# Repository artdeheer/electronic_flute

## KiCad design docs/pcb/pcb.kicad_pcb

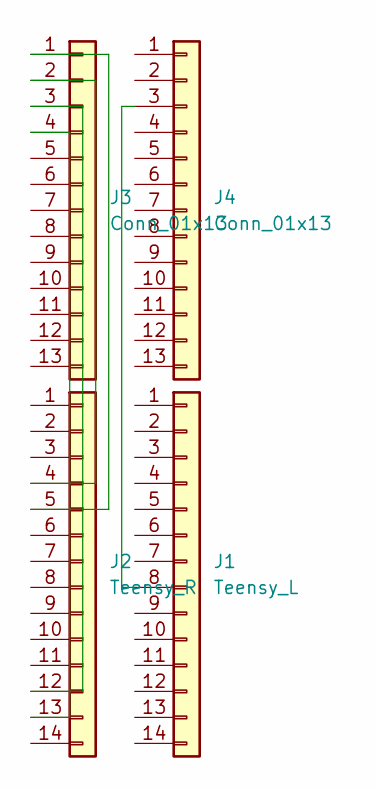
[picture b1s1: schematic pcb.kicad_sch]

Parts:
J1: Teensy_L; PinHeader_1x14_P2.54mm_Vertical
J2: Teensy_R; PinHeader_1x14_P2.54mm_Vertical
J3, J4: Conn_01x13; PinHeader_1x13_P2.54mm_Vertical

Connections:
unnamed: J1.8 (Pin_8_8), J4.3 (Pin_3_3)
unnamed: J2.4, J3.2
unnamed: J2.5, J3.1
unnamed: J2.12, J3.3
unnamed: J2.13, J3.4

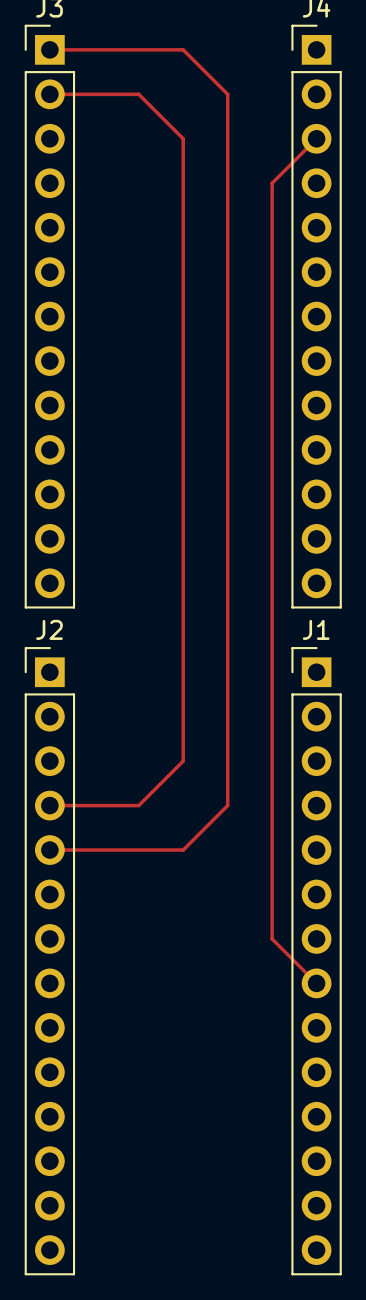
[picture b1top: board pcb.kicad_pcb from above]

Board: 2 copper layers, 4 parts (0 on the bottom side), 5 nets.

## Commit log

2026-04-24 basic code
2026-05-03 prototype
2026-05-03 docs
